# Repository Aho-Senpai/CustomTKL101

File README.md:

# CustomTKL101
Aho's CustomTKL101 PCB

This is the progression of my custom TKL-base Keyboard

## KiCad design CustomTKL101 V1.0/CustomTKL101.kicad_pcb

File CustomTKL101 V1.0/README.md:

This is the Achived V1.0.  
  
Main issues :  
- Does not have screwholes on the PCB

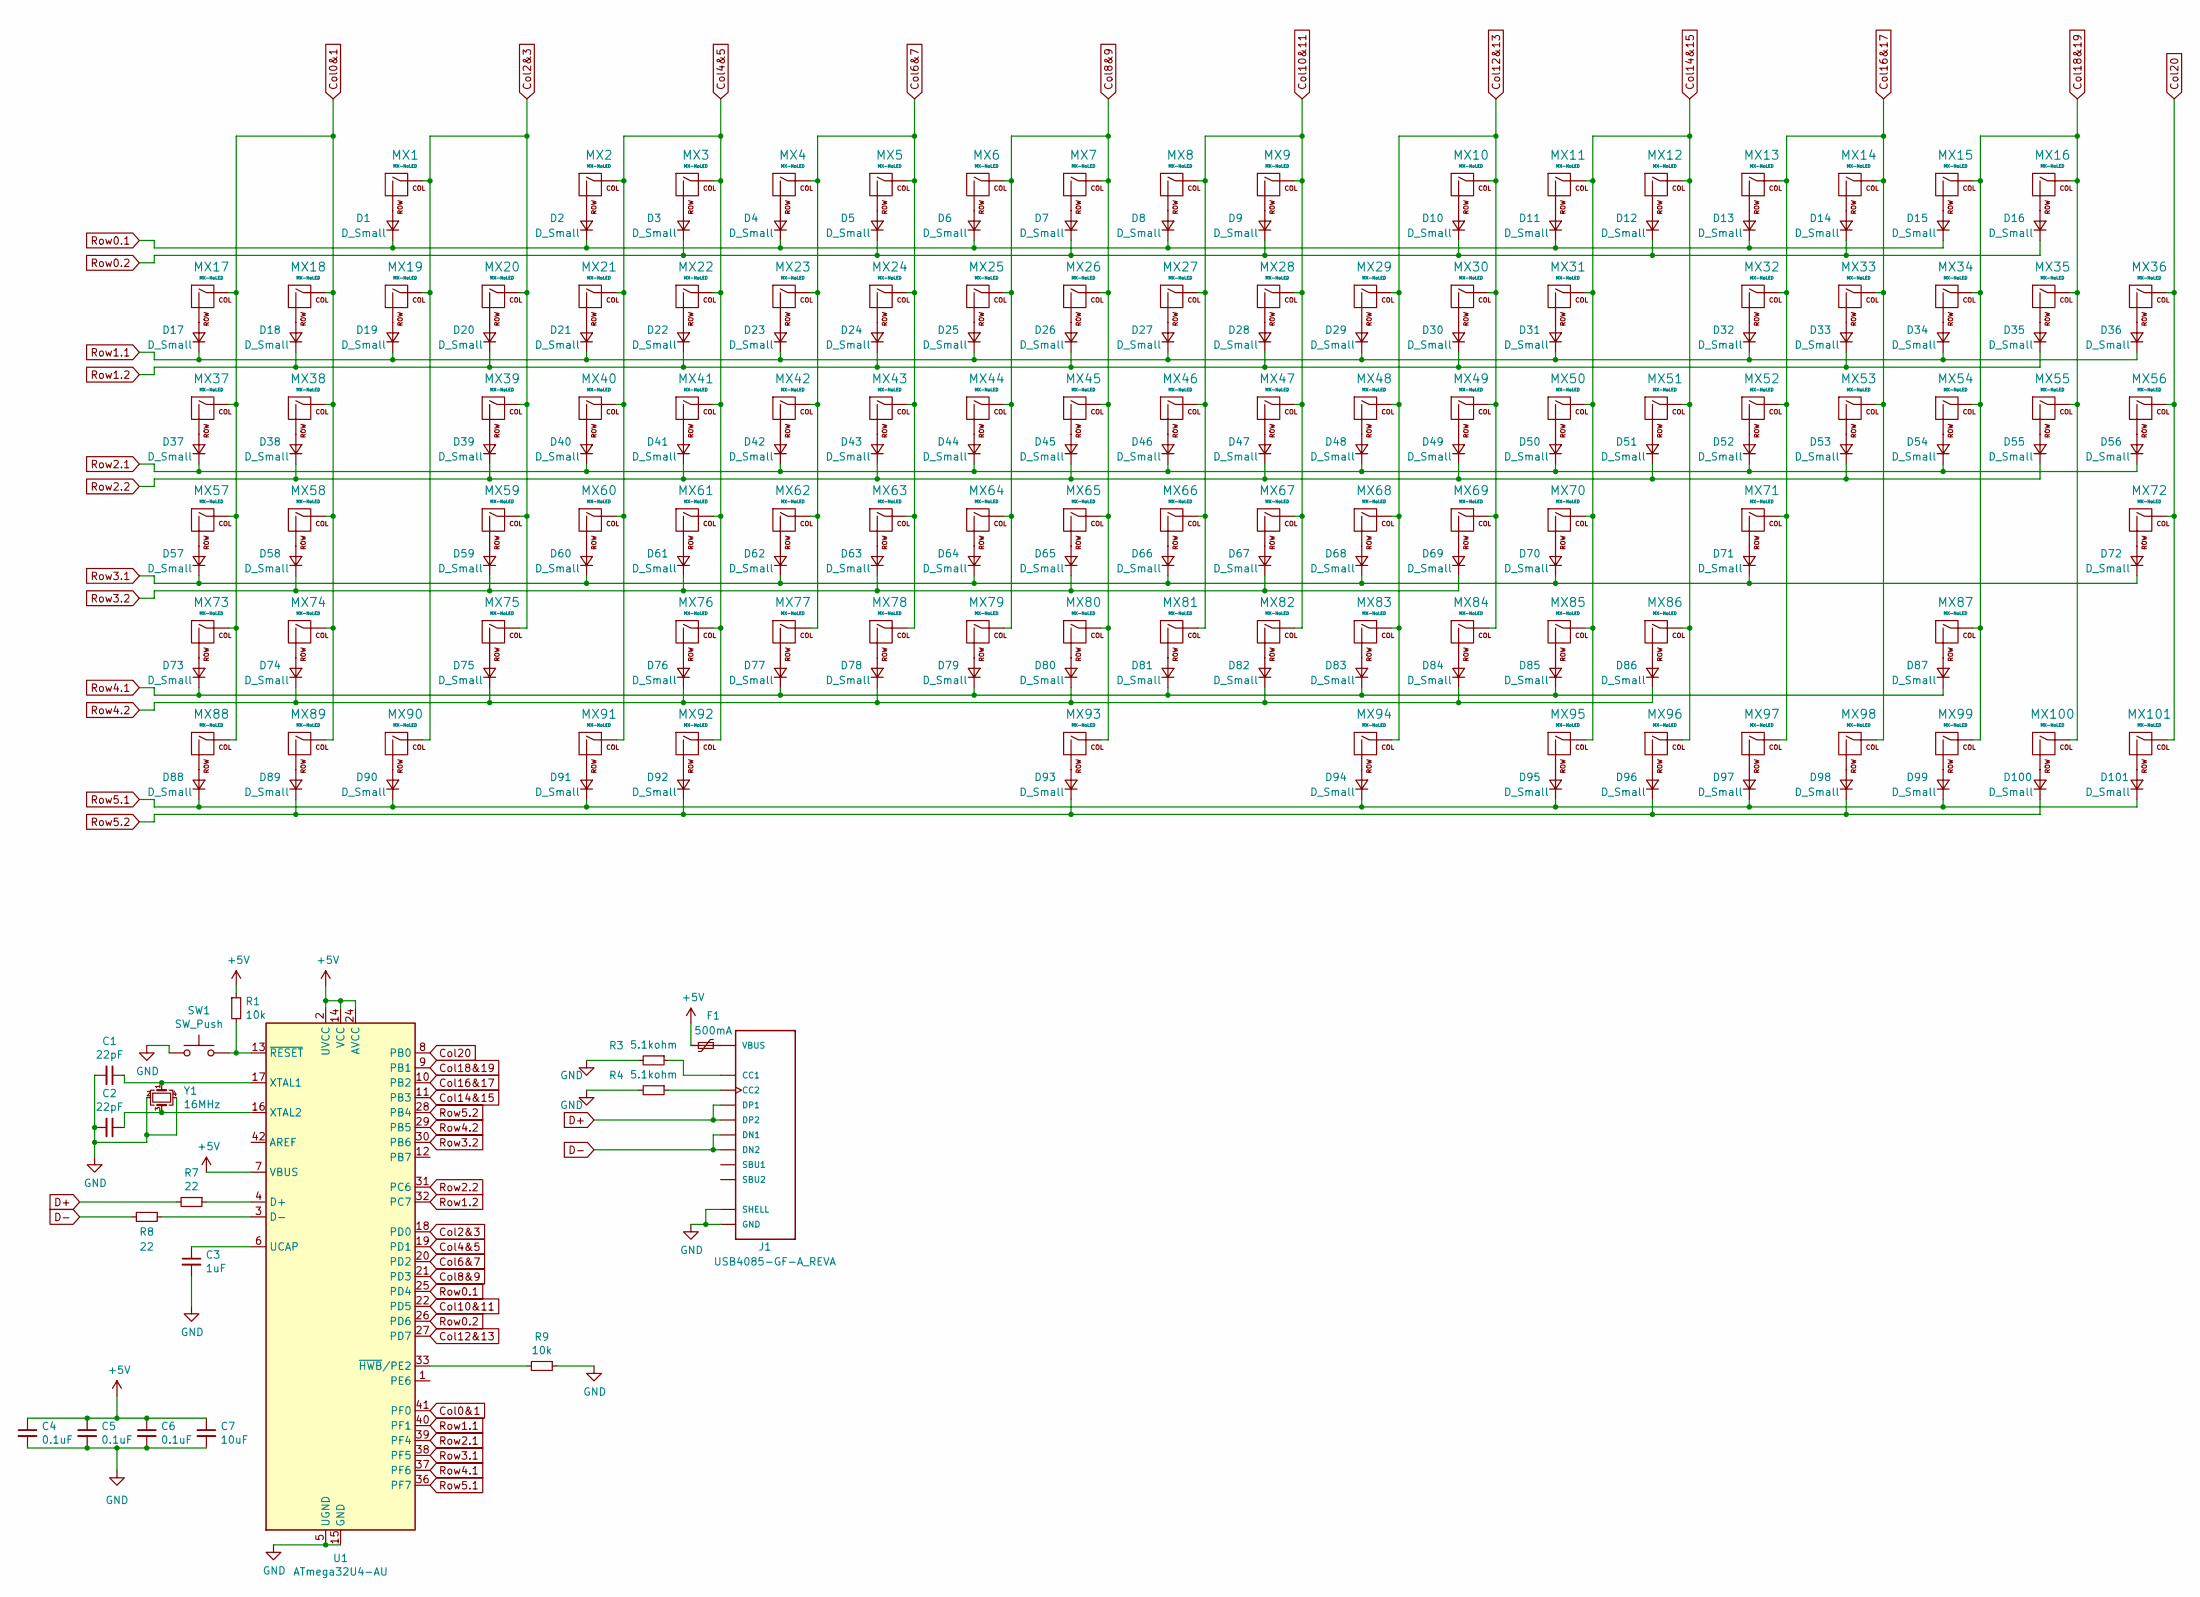
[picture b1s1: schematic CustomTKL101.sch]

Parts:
C1, C2: 22pF; C_0805_2012Metric
C3: 1uF; C_0805_2012Metric
C4, C5, C6: 0.1uF; C_0805_2012Metric
C7: 10uF; C_0805_2012Metric
D1, D2, D3, D4, D5, D6, D7, D8, D9, D10, D11, D12, D13, D14, D15, D16, D17, D18, D19, D20, D21, D22, D23, D24, D25, D26, D27, D28, D29, D30, D31, D32, D33, D34, D35, D36, D37, D38, D39, D40, D41, D42, D43, D44, D45, D46, D47, D48, D49, D50, D51, D52, D53, D54, D55, D56, D57, D58, D59, D60, D61, D62, D63, D64, D65, D66, D67, D68, D69, D70, D71, D72, D73, D74, D75, D76, D77, D78, D79, D80, D81, D82, D83, D84, D85, D86, D87, D88, D89, D90, D91, D92, D93, D94, D95, D96, D97, D98, D99, D100, D101: D_Small; D_SOD-123
F1: 500mA; Fuse_1206_3216Metric
J1: USB4085-GF-A_REVA; GCT_USB4085-GF-A_REVA
MX1, MX2, MX3, MX4, MX5, MX6, MX7, MX8, MX9, MX10, MX11, MX12, MX13, MX14, MX15, MX16, MX17, MX18, MX19, MX20, MX21, MX22, MX23, MX24, MX25, MX26, MX27, MX28, MX29, MX30, MX31, MX33, MX34, MX35, MX36, MX37, MX38, MX39, MX40, MX41, MX42, MX43, MX44, MX45, MX46, MX47, MX48, MX49, MX50, MX51, MX52, MX53, MX54, MX55, MX56, MX57, MX58, MX59, MX60, MX61, MX62, MX63, MX64, MX65, MX66, MX67, MX68, MX69, MX70, MX72, MX73, MX74, MX76, MX77, MX78, MX79, MX80, MX81, MX82, MX83, MX84, MX85, MX87, MX88, MX89, MX90, MX91, MX92, MX94, MX95, MX96, MX97, MX98, MX99, MX100: MX-NoLED; MX-1U-NoLED
MX32, MX101: MX-NoLED; MX-2U-ReversedStabilizers-NoLED
MX71, MX75: MX-NoLED; MX-2.25U-ReversedStabilizers-NoLED
MX86: MX-NoLED; MX-2.75U-ReversedStabilizers-NoLED
MX93: MX-NoLED; MX-6.25U-ReversedStabilizers-NoLED
R1, R9: 10k; R_0805_2012Metric
R3, R4: 5.1kohm; R_0805_2012Metric
R7, R8: 22; R_0805_2012Metric
SW1: SW_Push; SKQG-1155865
U1: ATmega32U4-AU; TQFP-44_10x10mm_P0.8mm
Y1: 16MHz; Crystal_SMD_3225-4Pin_3.2x2.5mm

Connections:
+5V: C4.1, C5.1, C6.1, C7.1, F1.2, R1.1, U1.2 (UVCC), U1.7 (VBUS), U1.14 (VCC), U1.24 (AVCC), U1.34 (VCC), U1.44 (AVCC)
Col0&1: MX17.1 (COL), MX18.1 (COL), MX37.1 (COL), MX38.1 (COL), MX57.1 (COL), MX58.1 (COL), MX73.1 (COL), MX74.1 (COL), MX88.1 (COL), MX89.1 (COL), U1.41 (PF0)
Col2&3: MX1.1 (COL), MX19.1 (COL), MX20.1 (COL), MX39.1 (COL), MX59.1 (COL), MX75.1 (COL), MX90.1 (COL), U1.18 (PD0)
Col4&5: MX2.1 (COL), MX3.1 (COL), MX21.1 (COL), MX22.1 (COL), MX40.1 (COL), MX41.1 (COL), MX60.1 (COL), MX61.1 (COL), MX76.1 (COL), MX91.1 (COL), MX92.1 (COL), U1.19 (PD1)
Col6&7: MX4.1 (COL), MX5.1 (COL), MX23.1 (COL), MX24.1 (COL), MX42.1 (COL), MX43.1 (COL), MX62.1 (COL), MX63.1 (COL), MX77.1 (COL), MX78.1 (COL), U1.20 (PD2)
Col8&9: MX6.1 (COL), MX7.1 (COL), MX25.1 (COL), MX26.1 (COL), MX44.1 (COL), MX45.1 (COL), MX64.1 (COL), MX65.1 (COL), MX79.1 (COL), MX80.1 (COL), MX93.1 (COL), U1.21 (PD3)
Col10&11: MX8.1 (COL), MX9.1 (COL), MX27.1 (COL), MX28.1 (COL), MX46.1 (COL), MX47.1 (COL), MX66.1 (COL), MX67.1 (COL), MX81.1 (COL), MX82.1 (COL), U1.22 (PD5)
Col12&13: MX10.1 (COL), MX29.1 (COL), MX30.1 (COL), MX48.1 (COL), MX49.1 (COL), MX68.1 (COL), MX69.1 (COL), MX83.1 (COL), MX84.1 (COL), MX94.1 (COL), U1.27 (PD7)
Col14&15: MX11.1 (COL), MX12.1 (COL), MX31.1 (COL), MX50.1 (COL), MX51.1 (COL), MX70.1 (COL), MX85.1 (COL), MX86.1 (COL), MX95.1 (COL), MX96.1 (COL), U1.11 (PB3)
Col16&17: MX13.1 (COL), MX14.1 (COL), MX32.1 (COL), MX33.1 (COL), MX52.1 (COL), MX53.1 (COL), MX71.1 (COL), MX97.1 (COL), MX98.1 (COL), U1.10 (PB2)
Col18&19: MX15.1 (COL), MX16.1 (COL), MX34.1 (COL), MX35.1 (COL), MX54.1 (COL), MX55.1 (COL), MX87.1 (COL), MX99.1 (COL), MX100.1 (COL), U1.9 (PB1)
Col20: MX36.1 (COL), MX56.1 (COL), MX72.1 (COL), MX101.1 (COL), U1.8 (PB0)
D+: J1.A6 (DP1), J1.B6 (DP2), R7.2
D-: J1.A7 (DN1), J1.B7 (DN2), R8.2
GND: C1.2, C2.2, C3.2, C4.2, C5.2, C6.2, C7.2, J1.A1 (GND), J1.A12 (GND), J1.B1 (GND), J1.B12 (GND), J1.P1 (SHELL), J1.P2 (SHELL), J1.P3 (SHELL), J1.P4 (SHELL), R3.2, R4.2, R9.1, SW1.1, U1.5 (UGND), U1.15 (GND), U1.23 (GND), U1.35 (GND), U1.43 (GND), Y1.2, Y1.4
unnamed: C1.1, U1.17 (XTAL1), Y1.1
unnamed: C2.1, U1.16 (XTAL2), Y1.3
unnamed: C3.1, U1.6 (UCAP)
unnamed: D1.2 (A), MX1.2 (ROW)
unnamed: D2.2 (A), MX2.2 (ROW)
unnamed: D3.2 (A), MX3.2 (ROW)
unnamed: D4.2 (A), MX4.2 (ROW)
unnamed: D5.2 (A), MX5.2 (ROW)
unnamed: D6.2 (A), MX6.2 (ROW)
unnamed: D7.2 (A), MX7.2 (ROW)
unnamed: D8.2 (A), MX8.2 (ROW)
unnamed: D9.2 (A), MX9.2 (ROW)
unnamed: D10.2 (A), MX10.2 (ROW)
unnamed: D11.2 (A), MX11.2 (ROW)
unnamed: D12.2 (A), MX12.2 (ROW)
unnamed: D13.2 (A), MX13.2 (ROW)
unnamed: D14.2 (A), MX14.2 (ROW)
unnamed: D15.2 (A), MX15.2 (ROW)
unnamed: D16.2 (A), MX16.2 (ROW)
unnamed: D17.2 (A), MX17.2 (ROW)
unnamed: D18.2 (A), MX18.2 (ROW)
unnamed: D19.2 (A), MX19.2 (ROW)
unnamed: D20.2 (A), MX20.2 (ROW)
unnamed: D21.2 (A), MX21.2 (ROW)
unnamed: D22.2 (A), MX22.2 (ROW)
unnamed: D23.2 (A), MX23.2 (ROW)
unnamed: D24.2 (A), MX24.2 (ROW)
unnamed: D25.2 (A), MX25.2 (ROW)
unnamed: D26.2 (A), MX26.2 (ROW)
unnamed: D27.2 (A), MX27.2 (ROW)
unnamed: D28.2 (A), MX28.2 (ROW)
unnamed: D29.2 (A), MX29.2 (ROW)
unnamed: D30.2 (A), MX30.2 (ROW)
unnamed: D31.2 (A), MX31.2 (ROW)
unnamed: D32.2 (A), MX32.2 (ROW)
unnamed: D33.2 (A), MX33.2 (ROW)
unnamed: D34.2 (A), MX34.2 (ROW)
unnamed: D35.2 (A), MX35.2 (ROW)
unnamed: D36.2 (A), MX36.2 (ROW)
unnamed: D37.2 (A), MX37.2 (ROW)
unnamed: D38.2 (A), MX38.2 (ROW)
unnamed: D39.2 (A), MX39.2 (ROW)
unnamed: D40.2 (A), MX40.2 (ROW)
unnamed: D41.2 (A), MX41.2 (ROW)
unnamed: D42.2 (A), MX42.2 (ROW)
unnamed: D43.2 (A), MX43.2 (ROW)
unnamed: D44.2 (A), MX44.2 (ROW)
unnamed: D45.2 (A), MX45.2 (ROW)
unnamed: D46.2 (A), MX46.2 (ROW)
unnamed: D47.2 (A), MX47.2 (ROW)
unnamed: D48.2 (A), MX48.2 (ROW)
unnamed: D49.2 (A), MX49.2 (ROW)
unnamed: D50.2 (A), MX50.2 (ROW)
unnamed: D51.2 (A), MX51.2 (ROW)
unnamed: D52.2 (A), MX52.2 (ROW)
unnamed: D53.2 (A), MX53.2 (ROW)
unnamed: D54.2 (A), MX54.2 (ROW)
unnamed: D55.2 (A), MX55.2 (ROW)
unnamed: D56.2 (A), MX56.2 (ROW)
unnamed: D57.2 (A), MX57.2 (ROW)
unnamed: D58.2 (A), MX58.2 (ROW)
unnamed: D59.2 (A), MX59.2 (ROW)
unnamed: D60.2 (A), MX60.2 (ROW)
unnamed: D61.2 (A), MX61.2 (ROW)
unnamed: D62.2 (A), MX62.2 (ROW)
unnamed: D63.2 (A), MX63.2 (ROW)
unnamed: D64.2 (A), MX64.2 (ROW)
unnamed: D65.2 (A), MX65.2 (ROW)
unnamed: D66.2 (A), MX66.2 (ROW)
unnamed: D67.2 (A), MX67.2 (ROW)
unnamed: D68.2 (A), MX68.2 (ROW)
unnamed: D69.2 (A), MX69.2 (ROW)
unnamed: D70.2 (A), MX70.2 (ROW)
unnamed: D71.2 (A), MX71.2 (ROW)
unnamed: D72.2 (A), MX72.2 (ROW)
unnamed: D73.2 (A), MX73.2 (ROW)
unnamed: D74.2 (A), MX74.2 (ROW)
unnamed: D75.2 (A), MX75.2 (ROW)
unnamed: D76.2 (A), MX76.2 (ROW)
unnamed: D77.2 (A), MX77.2 (ROW)
unnamed: D78.2 (A), MX78.2 (ROW)
unnamed: D79.2 (A), MX79.2 (ROW)
unnamed: D80.2 (A), MX80.2 (ROW)
unnamed: D81.2 (A), MX81.2 (ROW)
unnamed: D82.2 (A), MX82.2 (ROW)
unnamed: D83.2 (A), MX83.2 (ROW)
unnamed: D84.2 (A), MX84.2 (ROW)
unnamed: D85.2 (A), MX85.2 (ROW)
unnamed: D86.2 (A), MX86.2 (ROW)
unnamed: D87.2 (A), MX87.2 (ROW)
unnamed: D88.2 (A), MX88.2 (ROW)
unnamed: D89.2 (A), MX89.2 (ROW)
unnamed: D90.2 (A), MX90.2 (ROW)
unnamed: D91.2 (A), MX91.2 (ROW)
unnamed: D92.2 (A), MX92.2 (ROW)
unnamed: D93.2 (A), MX93.2 (ROW)
unnamed: D94.2 (A), MX94.2 (ROW)
unnamed: D95.2 (A), MX95.2 (ROW)
unnamed: D96.2 (A), MX96.2 (ROW)
unnamed: D97.2 (A), MX97.2 (ROW)
unnamed: D98.2 (A), MX98.2 (ROW)
unnamed: D99.2 (A), MX99.2 (ROW)
unnamed: D100.2 (A), MX100.2 (ROW)
unnamed: D101.2 (A), MX101.2 (ROW)
unnamed: F1.1, J1.A4 (VBUS), J1.A9 (VBUS), J1.B4 (VBUS), J1.B9 (VBUS)
unnamed: J1.A5 (CC1), R3.1
unnamed: J1.B5 (CC2), R4.1
unnamed: R1.2, SW1.2, U1.13 (~RESET)
unnamed: R7.1, U1.4 (D+)
unnamed: R8.1, U1.3 (D-)
unnamed: R9.2, U1.33 (~HWB~/PE2)
Row0.1: D1.1 (K), D2.1 (K), D4.1 (K), D6.1 (K), D8.1 (K), D11.1 (K), D13.1 (K), D15.1 (K), U1.25 (PD4)
Row0.2: D3.1 (K), D5.1 (K), D7.1 (K), D9.1 (K), D10.1 (K), D12.1 (K), D14.1 (K), D16.1 (K), U1.26 (PD6)
Row1.1: D17.1 (K), D19.1 (K), D21.1 (K), D23.1 (K), D25.1 (K), D27.1 (K), D29.1 (K), D31.1 (K), D32.1 (K), D34.1 (K), D36.1 (K), U1.40 (PF1)
Row1.2: D18.1 (K), D20.1 (K), D22.1 (K), D24.1 (K), D26.1 (K), D28.1 (K), D30.1 (K), D33.1 (K), D35.1 (K), U1.32 (PC7)
Row2.1: D37.1 (K), D40.1 (K), D42.1 (K), D44.1 (K), D46.1 (K), D48.1 (K), D50.1 (K), D52.1 (K), D54.1 (K), D56.1 (K), U1.39 (PF4)
Row2.2: D38.1 (K), D39.1 (K), D41.1 (K), D43.1 (K), D45.1 (K), D47.1 (K), D49.1 (K), D51.1 (K), D53.1 (K), D55.1 (K), U1.31 (PC6)
Row3.1: D57.1 (K), D60.1 (K), D62.1 (K), D64.1 (K), D66.1 (K), D68.1 (K), D70.1 (K), D71.1 (K), D72.1 (K), U1.38 (PF5)
Row3.2: D58.1 (K), D59.1 (K), D61.1 (K), D63.1 (K), D65.1 (K), D67.1 (K), D69.1 (K), U1.30 (PB6)
Row4.1: D73.1 (K), D77.1 (K), D79.1 (K), D81.1 (K), D83.1 (K), D85.1 (K), D87.1 (K), U1.37 (PF6)
Row4.2: D74.1 (K), D75.1 (K), D76.1 (K), D78.1 (K), D80.1 (K), D82.1 (K), D84.1 (K), D86.1 (K), U1.29 (PB5)
Row5.1: D88.1 (K), D90.1 (K), D91.1 (K), D94.1 (K), D95.1 (K), D97.1 (K), D99.1 (K), D101.1 (K), U1.36 (PF7)
Row5.2: D89.1 (K), D92.1 (K), D93.1 (K), D96.1 (K), D98.1 (K), D100.1 (K), U1.28 (PB4)

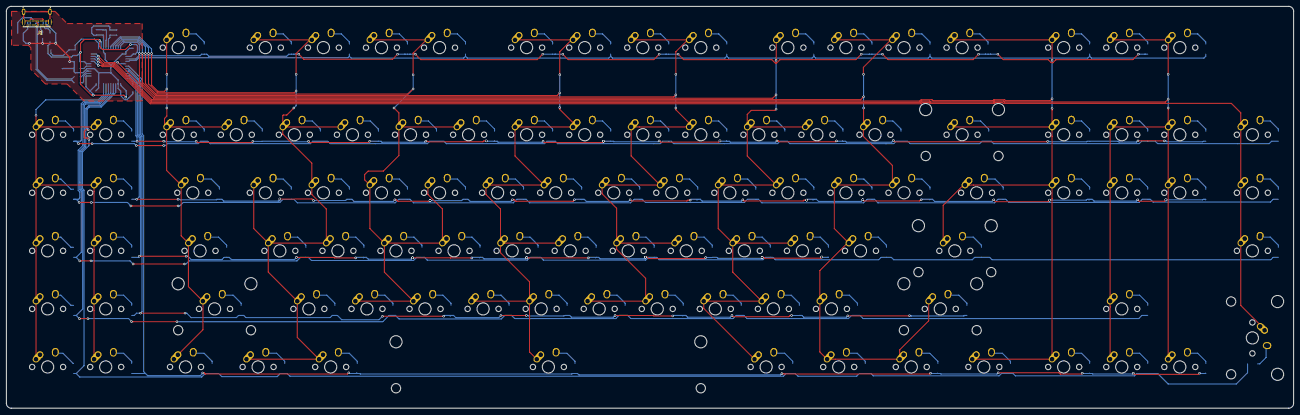
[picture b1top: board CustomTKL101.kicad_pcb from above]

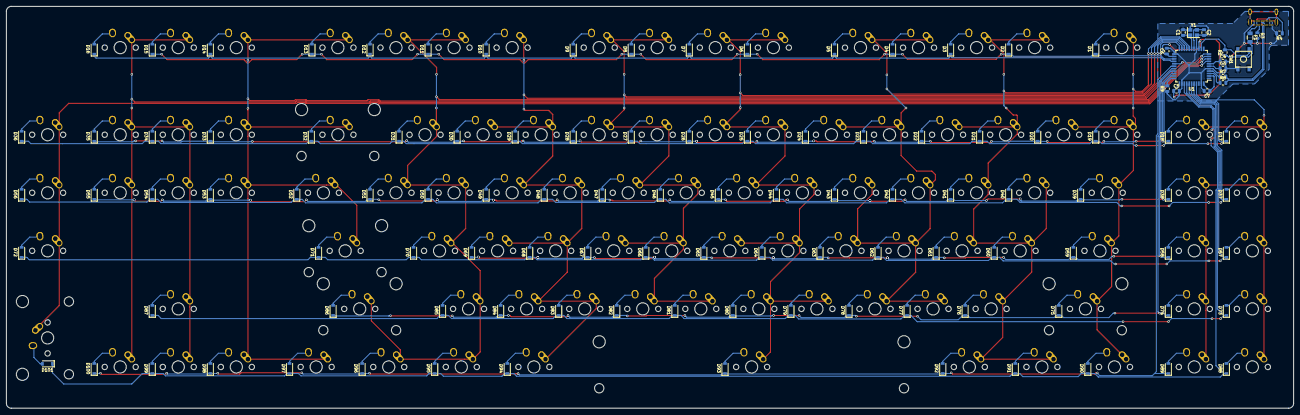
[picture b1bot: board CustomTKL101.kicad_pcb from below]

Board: 2 copper layers, 422.3 x 131.8 mm, 220 parts (118 on the bottom side), 138 nets.

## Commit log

2020-02-10 add submodules
2020-02-10 Create fp-lib-table
2020-02-10 fist fiddling
2020-02-10 Create fp-info-cache
2020-02-15 15-02-2020
2020-02-15 Schematic Progress
2020-02-15 Progress on Schematic
2020-02-15 Added Type-C submodule
2020-02-16 fixed global flags
2020-02-16 Board Progress
2020-02-17 tracing re-done
2020-02-17 changed numenter footprint
2020-02-17 Board Complete
2020-02-17 Removed dataline resistors
2020-02-17 routing fixing
2020-02-17 routing
2020-02-18 Completed PCB ?
2020-02-18 Lib Fix?
2020-02-18 Update CustomTKL101.kicad_pcb-bak
2020-02-18 Filled GND + Wiring fixes
2020-02-18 Finalised PCB
    Finalised PCB and sent to prod, waiting for results
2020-05-25 Archive V1.0
    Put in it's own folder
